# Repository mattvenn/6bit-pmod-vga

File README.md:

# 6bit PMOD VGA

Used in a few projects 

* ASIC clock - https://github.com/mattvenn/vga-clock
* Craposcope - https://github.com/mattvenn/crap-o-scope

# PCB

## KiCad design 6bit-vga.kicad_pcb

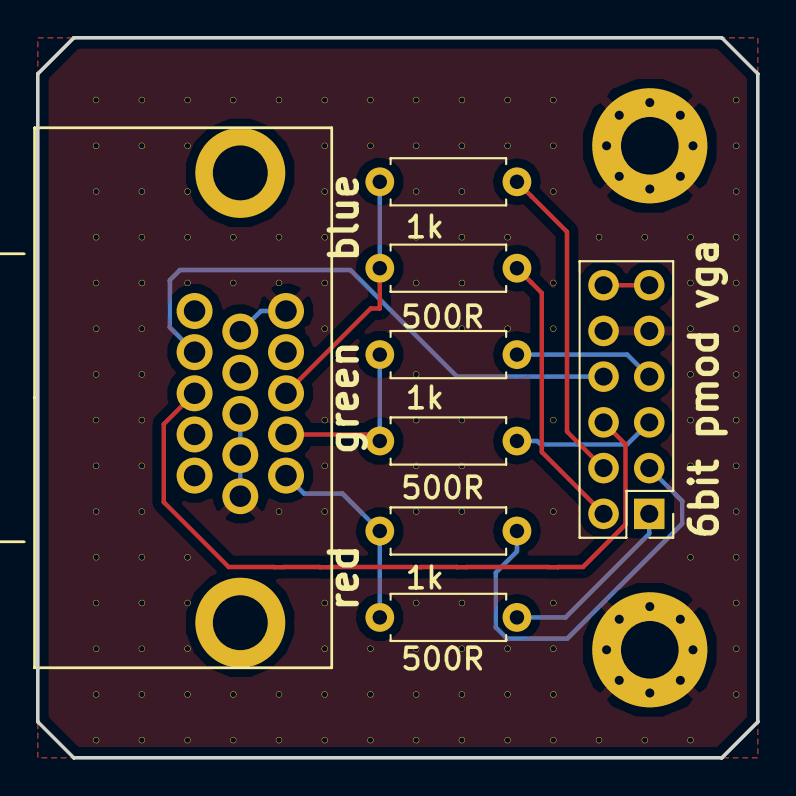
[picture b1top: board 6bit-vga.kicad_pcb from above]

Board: 2 copper layers, 40.0 x 40.0 mm, 149 parts (0 on the bottom side), 13 nets.

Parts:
J1: pmod; Pin_Header_Straight_2x06_Pitch2.54mm
J2, J3: Conn_01x01; MountingHole_3.2mm_M3_Pad_Via
J4: DB15_Female_HighDensity; db15
R2, R4, R6: 500R; R_Axial_DIN0207_L6.3mm_D2.5mm_P7.62mm_Horizontal
R3, R5, R7: 1k; R_Axial_DIN0207_L6.3mm_D2.5mm_P7.62mm_Horizontal
V6_4, V6_5, V6_6, V6_7, V6_8, V6_9, V6_10, V6_11, V6_12, V6_13, V6_14, V6_15, V6_16, V6_17, V6_18, V7_4, V7_5, V7_6, V7_7, V7_8, V7_9, V7_10, V7_11, V7_12, V7_13, V7_14, V7_15, V7_16, V7_17, V7_18, V8_4, V8_5, V8_6, V8_7, V8_8, V8_14, V8_15, V8_16, V8_17, V8_18, V9_4, V9_7, V9_8, V9_17, V9_18, V10_4, V10_7, V10_8, V10_13, V10_17, V10_18, V11_4, V11_5, V11_6, V11_7, V11_8, V11_9, V11_11, V11_12, V11_13, V11_15, V11_16, V11_17, V11_18, V12_4, V12_5, V12_16, V12_17, V12_18, V13_4, V13_5, V13_6, V13_7, V13_8, V13_10, V13_11, V13_12, V13_13, V13_15, V13_16, V13_17, V13_18, V14_4, V14_5, V14_6, V14_7, V14_8, V14_9, V14_11, V14_12, V14_13, V14_15, V14_16, V14_17, V14_18, V15_4, V15_5, V15_7, V15_9, V15_16, V15_17, V15_18, V16_4, V16_5, V16_6, V16_8, V16_9, V16_11, V16_13, V16_15, V16_16, V16_17, V16_18, V17_7, V17_18, V18_7, V18_18, V19_7, V19_8, V19_9, V19_10, V19_11, V19_12, V19_14, V19_18, V20_4, V20_5, V20_6, V20_7, V20_8, V20_9, V20_10, V20_11, V20_12, V20_13, V20_14, V20_15, V20_16, V20_17: AUTO_VIA; VIA_MATRIX

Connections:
/b1: J1.2, R6.2
/b2: J1.4, R7.2
/blue: J4.3, R6.1, R7.1
/g1: J1.5, R4.2
/g2: J1.7, R5.2
/green: J4.2, R4.1, R5.1
/hsync: J1.6, J4.13
/r1: J1.1, R2.2
/r2: J1.3, R3.2
/red: J4.1, R2.1, R3.1
/vsync: J1.8, J4.14
Earth: J1.9, J1.10, J2.1, J3.1, J4.5, J4.6, J4.7, J4.8, J4.10, V6_4.1, V6_5.1, V6_6.1, V6_7.1, V6_8.1, V6_9.1, V6_10.1, V6_11.1, V6_12.1, V6_13.1, V6_14.1, V6_15.1, V6_16.1, V6_17.1, V6_18.1, V7_4.1, V7_5.1, V7_6.1, V7_7.1, V7_8.1, V7_9.1, V7_10.1, V7_11.1, V7_12.1, V7_13.1, V7_14.1, V7_15.1, V7_16.1, V7_17.1, V7_18.1, V8_4.1, V8_5.1, V8_6.1, V8_7.1, V8_8.1, V8_14.1, V8_15.1, V8_16.1, V8_17.1, V8_18.1, V9_4.1, V9_7.1, V9_8.1, V9_17.1, V9_18.1, V10_4.1, V10_7.1, V10_8.1, V10_13.1, V10_17.1, V10_18.1, V11_4.1, V11_5.1, V11_6.1, V11_7.1, V11_8.1, V11_9.1, V11_11.1, V11_12.1, V11_13.1, V11_15.1, V11_16.1, V11_17.1, V11_18.1, V12_4.1, V12_5.1, V12_16.1, V12_17.1, V12_18.1, V13_4.1, V13_5.1, V13_6.1, V13_7.1, V13_8.1, V13_10.1, V13_11.1, V13_12.1, V13_13.1, V13_15.1, V13_16.1, V13_17.1, V13_18.1, V14_4.1, V14_5.1, V14_6.1, V14_7.1, V14_8.1, V14_9.1, V14_11.1, V14_12.1, V14_13.1, V14_15.1, V14_16.1, V14_17.1, V14_18.1, V15_4.1, V15_5.1, V15_7.1, V15_9.1, V15_16.1, V15_17.1, V15_18.1, V16_4.1, V16_5.1, V16_6.1, V16_8.1, V16_9.1, V16_11.1, V16_13.1, V16_15.1, V16_16.1, V16_17.1, V16_18.1, V17_7.1, V17_18.1, V18_7.1, V18_18.1, V19_7.1, V19_8.1, V19_9.1, V19_10.1, V19_11.1, V19_12.1, V19_14.1, V19_18.1, V20_4.1, V20_5.1, V20_6.1, V20_7.1, V20_8.1, V20_9.1, V20_10.1, V20_11.1, V20_12.1, V20_13.1, V20_14.1, V20_15.1, V20_16.1, V20_17.1
VCC: J1.11, J1.12

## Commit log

2018-05-07 updated silk to show values, made refs invisible
2018-05-07 missing fp
2018-05-18 schematic and board
2018-05-18 project file
2018-05-28 fixed bad fp
2021-07-02 cache lib
2022-02-28 update kicad6
2022-02-28 docs and kicad6 update
2022-02-28 update pcb and readme
